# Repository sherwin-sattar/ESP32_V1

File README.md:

# ESP32 V1.0 (micro USB)

## 3D views

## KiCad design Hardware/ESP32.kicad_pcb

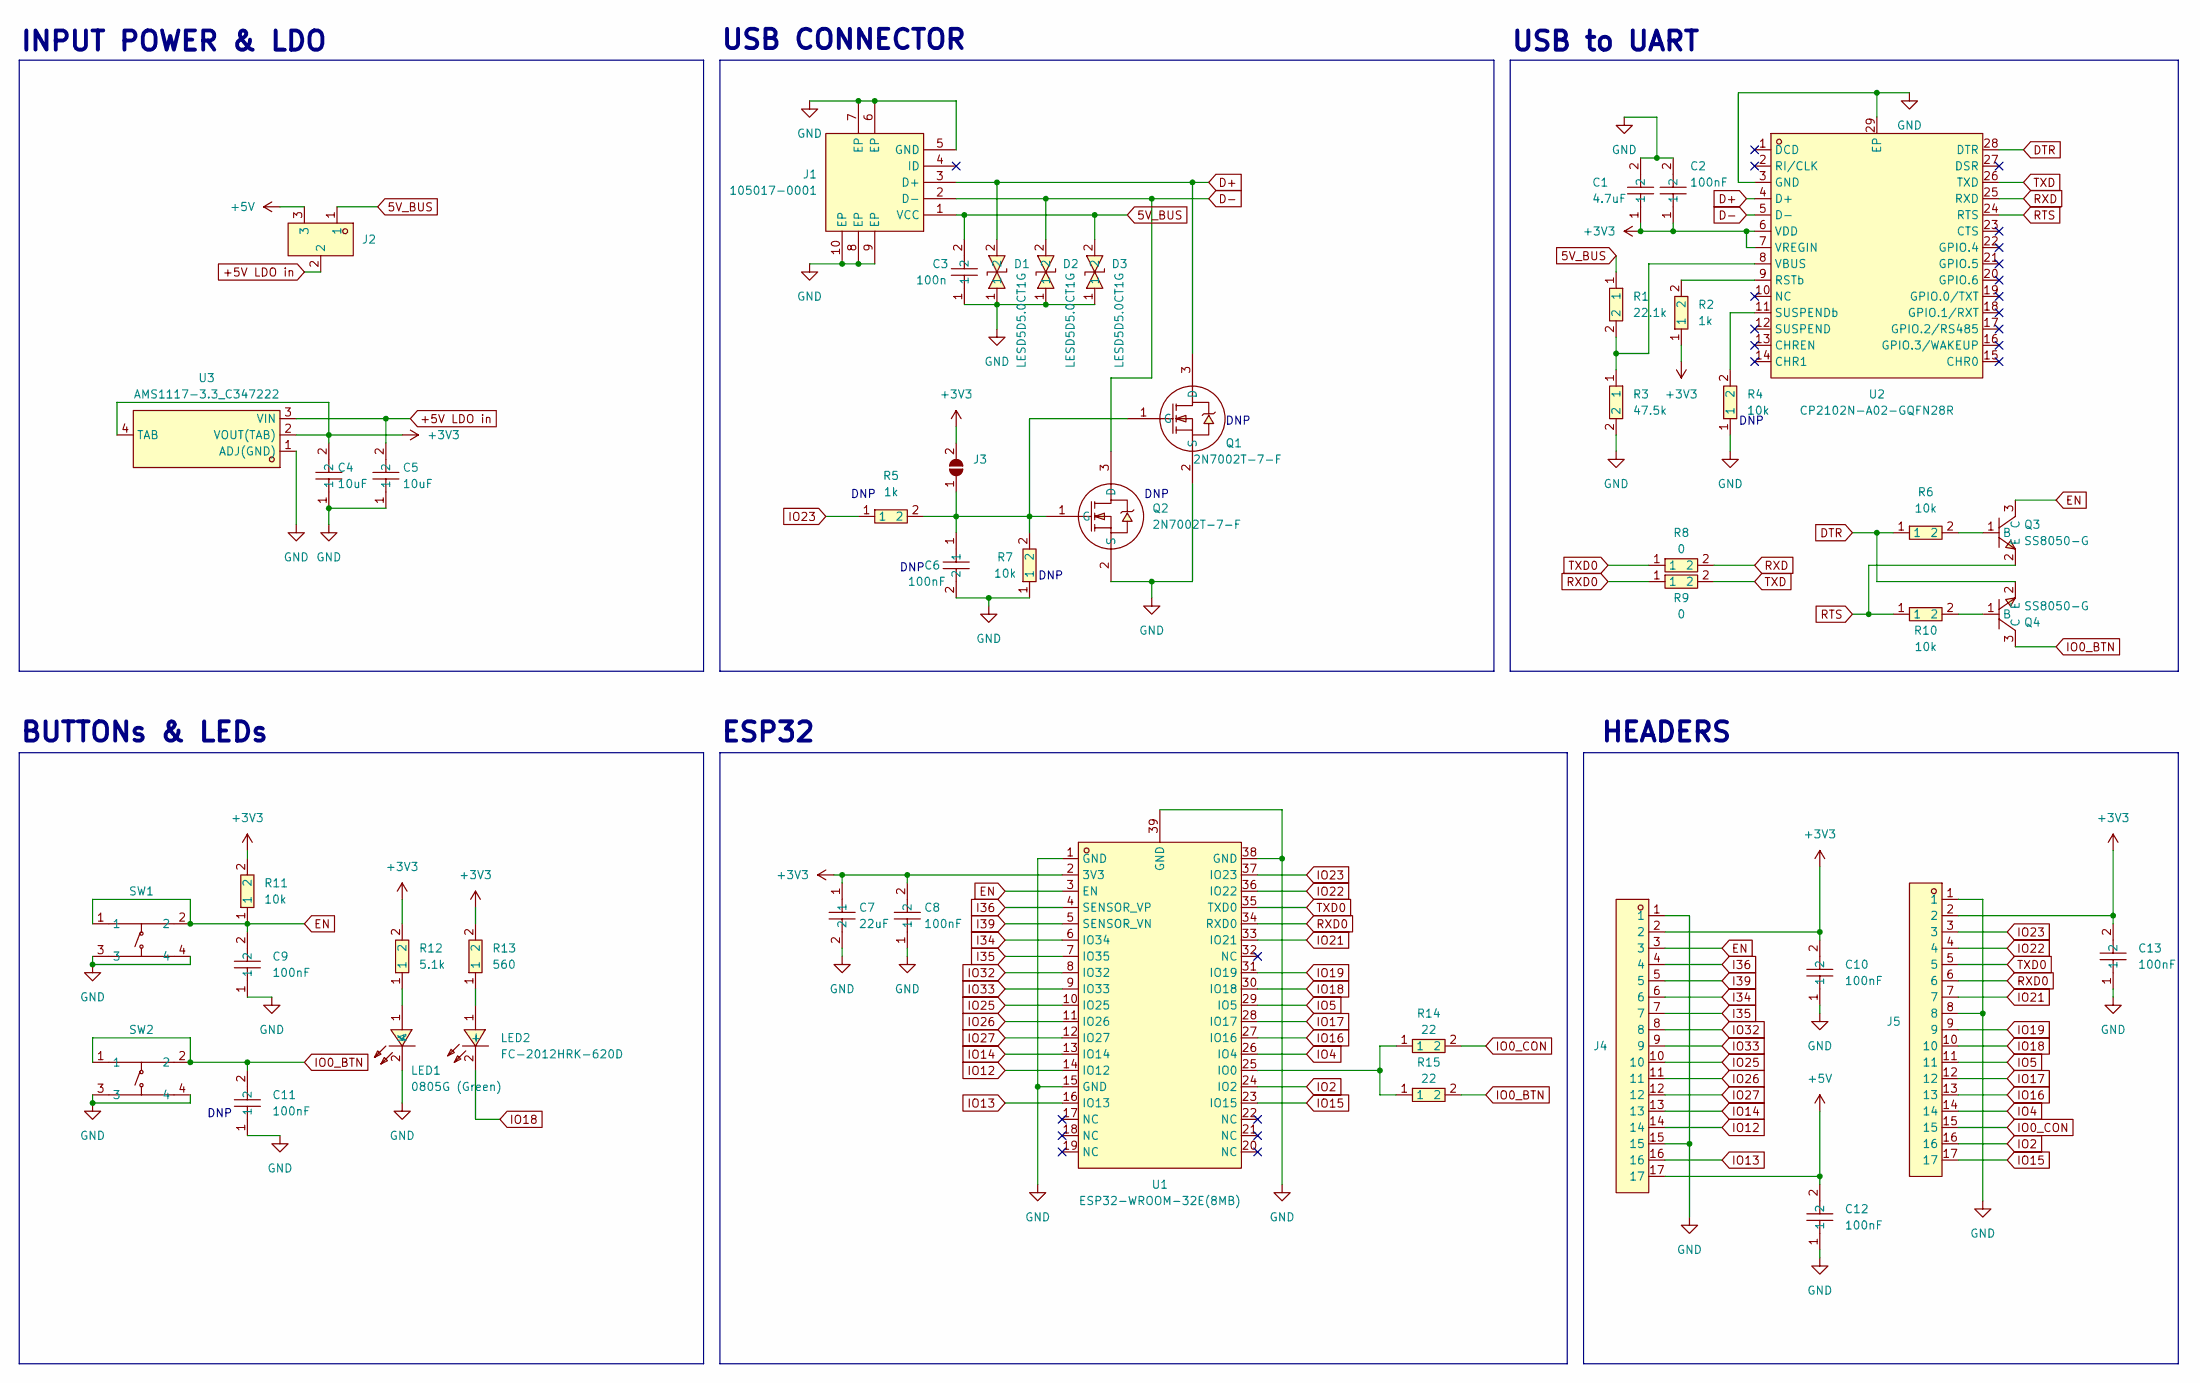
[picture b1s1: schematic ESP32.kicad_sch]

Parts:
C1: 4.7uF; C0402; LCSC Part C368809
C2, C6, C8, C9, C10, C11, C12, C13: 100nF; C0402; LCSC Part C1525
C3: 100n; C0402; LCSC Part C1525
C4, C5: 10uF; C0402; LCSC Part C315248
C7: 22uF; C0805; LCSC Part C602037
D1, D2, D3: LESD5D5.0CT1G; SOD-523_L1.2-W0.8-LS1.6-BI; LCSC Part C383211
J1: 105017-0001; MICRO-USB-SMD_105017-0001; LCSC Part C136000
J2: X1311WVS-03J-C40D42R2; HDR-SMD_3P-P1.27-V-M-LS4.2_X1311WVS-03J-C40D42R2; LCSC Part C5243526
J3: SolderJumper_2_Open; SolderJumper-2_P1.3mm_Open_RoundedPad1.0x1.5mm
J4, J5: X6511WV-17H-C30D60; HDR-TH_17P-P2.54-V-M; LCSC Part C725949
LED1: 0805G (Green); LED0805-R-RD; LCSC Part C2297
LED2: FC-2012HRK-620D; LED0805-R-RD; LCSC Part C84256
Q1, Q2: 2N7002T-7-F; SOT-523-3_L1.6-W0.8-P1.00-LS1.6-BR; LCSC Part C139445
Q3, Q4: SS8050-G; SOT-23-3_L2.9-W1.3-P1.90-LS2.4-BR; LCSC Part C164886
R1: 22.1k; R0402; LCSC Part C43473
R2, R5: 1k; R0402; LCSC Part C11702
R3: 47.5k; R0402; LCSC Part C25896
R4, R6, R7, R10, R11: 10k; R0402; LCSC Part C25744
R8, R9: 0; R0402; LCSC Part C17168
R12: 5.1k; R0402; LCSC Part C25905
R13: 560; R0402; LCSC Part C25126
R14, R15: 22; R0402; LCSC Part C25092
SW1, SW2: PTS645SH50SMTR92LFS; KEY-SMD_4P-L6.0-W6.0-P4.50-LS9.0; LCSC Part C221869
U1: ESP32-WROOM-32E(8MB); WIFI-SMD_ESP32-WROOM-32E; LCSC Part C701342
U2: CP2102N-A02-GQFN28R; QFN-28_L5.0-W5.0-P0.50-TL-EP3.3; LCSC Part C964632
U3: AMS1117-3.3_C347222; SOT-223-4_L6.5-W3.5-P2.30-LS7.0-BR; LCSC Part C347222

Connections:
5V_BUS: C3.2, D3.2, J1.1 (VCC), J2.1, R1.1
+3V3: C1.1, C2.1, C4.2, C7.1, C8.2, C10.2, C13.2, J3.2 (B), J4.2, J5.2, R2.1, R11.2, R12.2, R13.2, U1.2 (3V3), U2.6 (VDD), U2.7 (VREGIN), U3.2 (VOUT(TAB)), U3.4 (TAB)
+5V: C12.2, J2.3, J4.17
+5V LDO in: C5.2, J2.2, U3.3 (VIN)
D+: D1.2, J1.3 (D+), Q1.3 (D), U2.4 (D+)
D-: D2.2, J1.2 (D-), Q2.3 (D), U2.5 (D-)
DTR: Q4.2 (E), R6.1, U2.28 (DTR)
EN: C9.2, J4.3, Q3.3 (C), R11.1, SW1.1, SW1.2, U1.3 (EN)
GND: C1.2, C2.2, C3.1, C4.1, C5.1, C6.2, C7.2, C8.1, C9.1, C10.1, C11.1, C12.1, C13.1, D1.1, D2.1, D3.1, J1.5 (GND), J1.6 (EP), J1.7 (EP), J1.8 (EP), J1.9 (EP), J1.10 (EP), J4.1, J4.15, J5.1, J5.8, LED1.2 (K), Q1.2 (S), Q2.2 (S), R3.2, R4.1, R7.1, SW1.3, SW1.4, SW2.3, SW2.4, U1.1 (GND), U1.15 (GND), U1.38 (GND), U1.39 (GND), U2.3 (GND), U2.29 (EP), U3.1 (ADJ(GND))
I34: J4.6, U1.6 (IO34)
I35: J4.7, U1.7 (IO35)
I36: J4.4, U1.4 (SENSOR_VP)
I39: J4.5, U1.5 (SENSOR_VN)
IO0_BTN: C11.2, Q4.3 (C), R15.2, SW2.1, SW2.2
IO0_CON: J5.15, R14.2
IO2: J5.16, U1.24 (IO2)
IO4: J5.14, U1.26 (IO4)
IO5: J5.11, U1.29 (IO5)
IO12: J4.14, U1.14 (IO12)
IO13: J4.16, U1.16 (IO13)
IO14: J4.13, U1.13 (IO14)
IO15: J5.17, U1.23 (IO15)
IO16: J5.13, U1.27 (IO16)
IO17: J5.12, U1.28 (IO17)
IO18: J5.10, LED2.2 (-), U1.30 (IO18)
IO19: J5.9, U1.31 (IO19)
IO21: J5.7, U1.33 (IO21)
IO22: J5.4, U1.36 (IO22)
IO23: J5.3, R5.1, U1.37 (IO23)
IO25: J4.10, U1.10 (IO25)
IO26: J4.11, U1.11 (IO26)
IO27: J4.12, U1.12 (IO27)
IO32: J4.8, U1.8 (IO32)
IO33: J4.9, U1.9 (IO33)
unnamed: C6.1, J3.1 (A), Q1.1 (G), Q2.1 (G), R5.2, R7.2
unnamed: LED1.1 (A), R12.1
unnamed: LED2.1 (+), R13.1
unnamed: Q3.1 (B), R6.2
unnamed: Q4.1 (B), R10.2
unnamed: R14.1, R15.1, U1.25 (IO0)
unnamed: R2.2, U2.9 (RSTb)
unnamed: R4.2, U2.11 (SUSPENDb)
unnamed: R1.2, R3.1, U2.8 (VBUS)
RTS: Q3.2 (E), R10.1, U2.24 (RTS)
RXD: R8.2, U2.25 (RXD)
RXD0: J5.6, R9.1, U1.34 (RXD0)
TXD: R9.2, U2.26 (TXD)
TXD0: J5.5, R8.1, U1.35 (TXD0)

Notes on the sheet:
DNP
ESP32
HEADERS
BUTTONs & LEDs
USB CONNECTOR
INPUT POWER & LDO
USB to UART

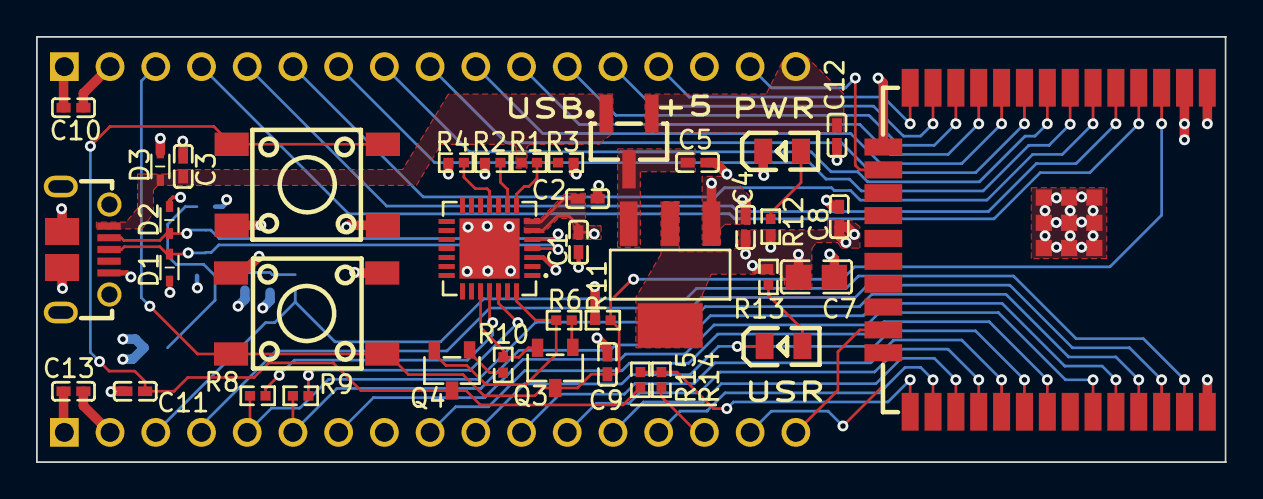
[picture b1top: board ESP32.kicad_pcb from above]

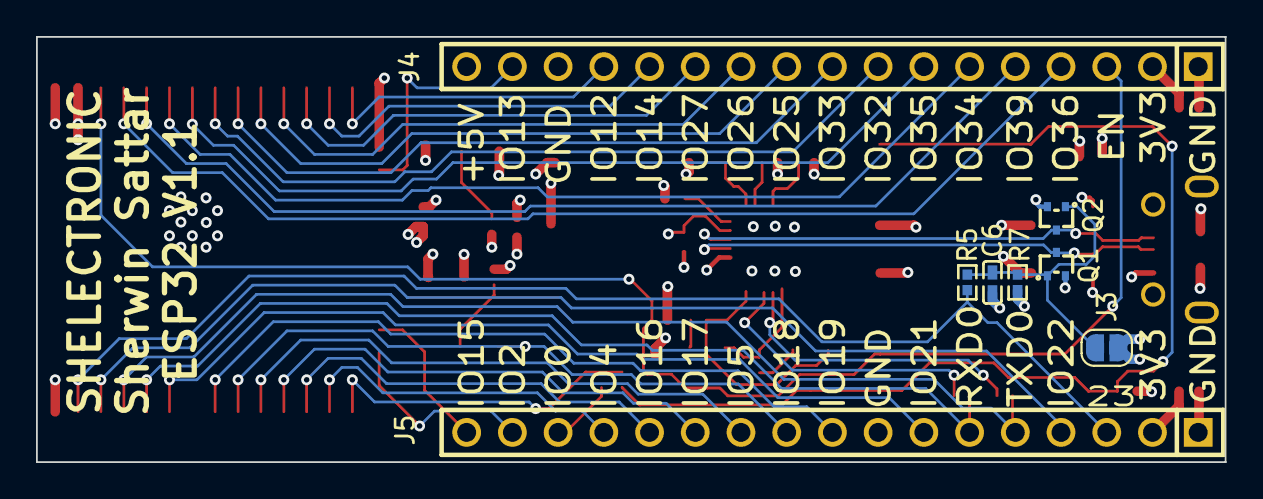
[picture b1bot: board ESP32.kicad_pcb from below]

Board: 4 copper layers, 66.0 x 23.6 mm, 47 parts (8 on the bottom side), 48 nets.
